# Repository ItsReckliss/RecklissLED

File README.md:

# RecklissLED

LED strip PCBs designed in [KiCad](https://www.kicad.org/) 10.

> Work in progress: schematic and board layout for the 34x7 strip have just been started.

## Layout

```
34x7/
├── design/RecklissLED 34x7/    KiCad project (open the .kicad_pro)
│   ├── EasyEDA.kicad_sym       project symbol library
│   ├── EasyEDA.pretty/         project footprint library
│   ├── EasyEDA.3dshapes/       3D models (.step / .wrl)
│   └── RecklissLED 34x7.kicad_dru   JLCPCB design rules
├── images/                     renders and photos
└── manufacturing/              Gerbers and BOM for orders
```

## Opening the project

Clone the repo and open `34x7/design/RecklissLED 34x7/RecklissLED 34x7.kicad_pro` in KiCad 10.

The project is self-contained: every part's symbol, footprint and 3D model lives in the project folder and is referenced with `${KIPRJMOD}` paths, so nothing extra needs installing.

## Adding parts

LCSC/JLCPCB parts are imported with the [impartGUI plugin](https://github.com/Steffen-W/Import-LIB-KiCad-Plugin):

- Launch it from the **PCB Editor** (Tools → External Plugins → impartGUI). From the Schematic Editor it can't detect the open project.
- Tick **Save local, in the project folder**; leave **auto settings** unticked. The `EasyEDA` library is already in the project's library tables.

## Design rules

`RecklissLED 34x7.kicad_dru` holds JLCPCB 2-layer, 1 oz copper rules from [Cimos/kicad-druid](https://github.com/Cimos/kicad-druid). Run **Inspect → Design Rules Checker** before exporting Gerbers.

## Working on it from multiple computers

1. `git pull` before opening KiCad.
2. When you're done: save, close KiCad, then `git add -A`, `git commit`, `git push`.
3. Only edit a board on one computer at a time. KiCad files don't merge well.

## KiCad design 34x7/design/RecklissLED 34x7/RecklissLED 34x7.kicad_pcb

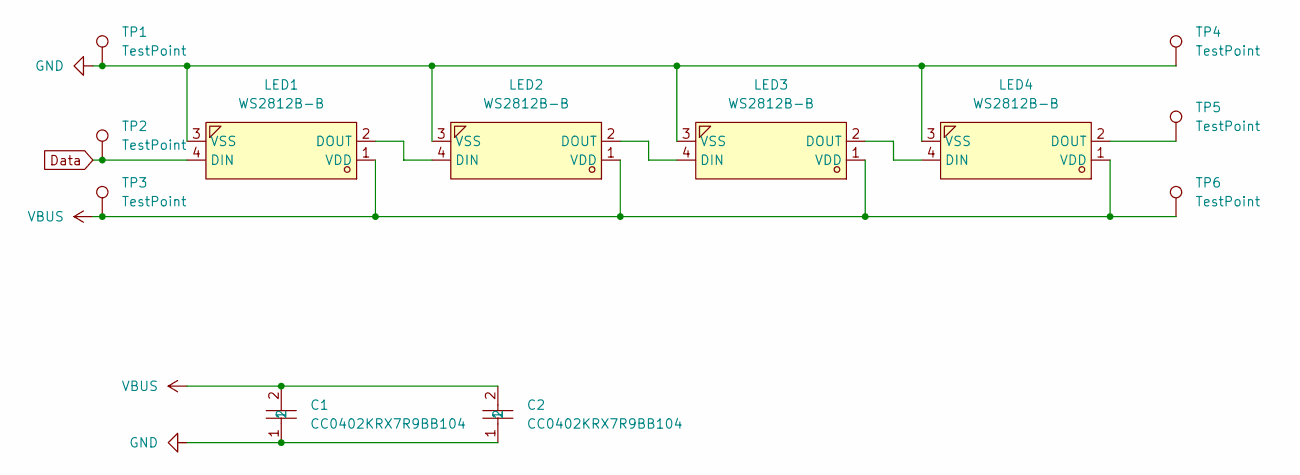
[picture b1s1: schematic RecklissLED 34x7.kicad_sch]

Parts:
C1, C2: CC0402KRX7R9BB104; C0402; MPN CC0402KRX7R9BB104; LCSC Part C131394
LED1, LED2, LED3, LED4: WS2812B-B; LED-SMD_4P-L5.0-W5.0-BL_TC5050RGB; MPN WS2812B-B/W; LCSC Part C114586
TP1, TP2, TP3, TP4, TP5, TP6: TestPoint; SolderWirePad_1x01_SMD_1x2mm

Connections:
Data: LED1.4 (DIN), TP2.1 (1_1)
GND: C1.1, C2.1, LED1.3 (VSS), LED2.3 (VSS), LED3.3 (VSS), LED4.3 (VSS), TP1.1 (1_1), TP4.1 (1_1)
unnamed: LED1.2 (DOUT), LED2.4 (DIN)
unnamed: LED2.2 (DOUT), LED3.4 (DIN)
unnamed: LED3.2 (DOUT), LED4.4 (DIN)
unnamed: LED4.2 (DOUT), TP5.1 (1_1)
VBUS: C1.2, C2.2, LED1.1 (VDD), LED2.1 (VDD), LED3.1 (VDD), LED4.1 (VDD), TP3.1 (1_1), TP6.1 (1_1)

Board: 2 copper layers, 12 parts (0 on the bottom side), 7 nets, no tracks yet.
